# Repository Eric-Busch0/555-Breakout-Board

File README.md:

# 555-Breakout-Board
Simple PCB for the infamous 555 timer fixed at ~1kHz

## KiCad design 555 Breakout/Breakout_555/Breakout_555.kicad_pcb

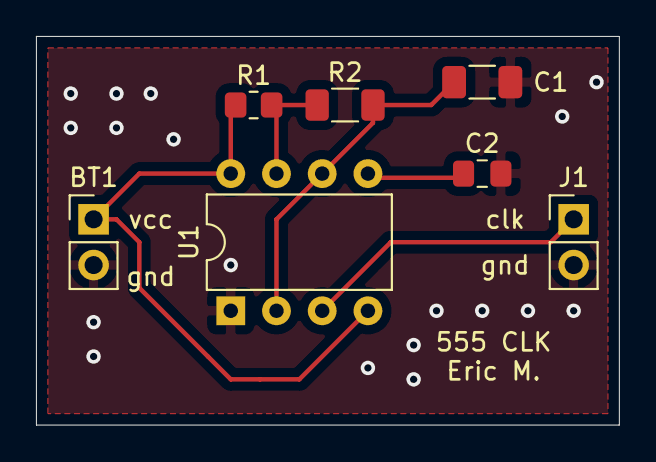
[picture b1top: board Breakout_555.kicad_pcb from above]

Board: 2 copper layers, 32.4 x 21.6 mm, 7 parts (0 on the bottom side), 6 nets.

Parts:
BT1: 9v; PinHeader_1x02_P2.54mm_Vertical
C1: 68n; C_1206_3216Metric_Pad1.33x1.80mm_HandSolder
C2: 10n; C_0805_2012Metric_Pad1.18x1.45mm_HandSolder
J1: terminal; PinHeader_1x02_P2.54mm_Vertical
R1: 220; R_0805_2012Metric_Pad1.20x1.40mm_HandSolder
R2: 10k; R_1206_3216Metric_Pad1.30x1.75mm_HandSolder
U1: NE555P; DIP-8_W7.62mm

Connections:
+9V: BT1.1, R1.1, U1.4, U1.8
/clk: J1.1, U1.3
/dis: R1.2, R2.1, U1.7
/trig_thrs: C1.1, R2.2, U1.2, U1.6
GND: BT1.2, C1.2, C2.2, J1.2, U1.1
unnamed: C2.1, U1.5
